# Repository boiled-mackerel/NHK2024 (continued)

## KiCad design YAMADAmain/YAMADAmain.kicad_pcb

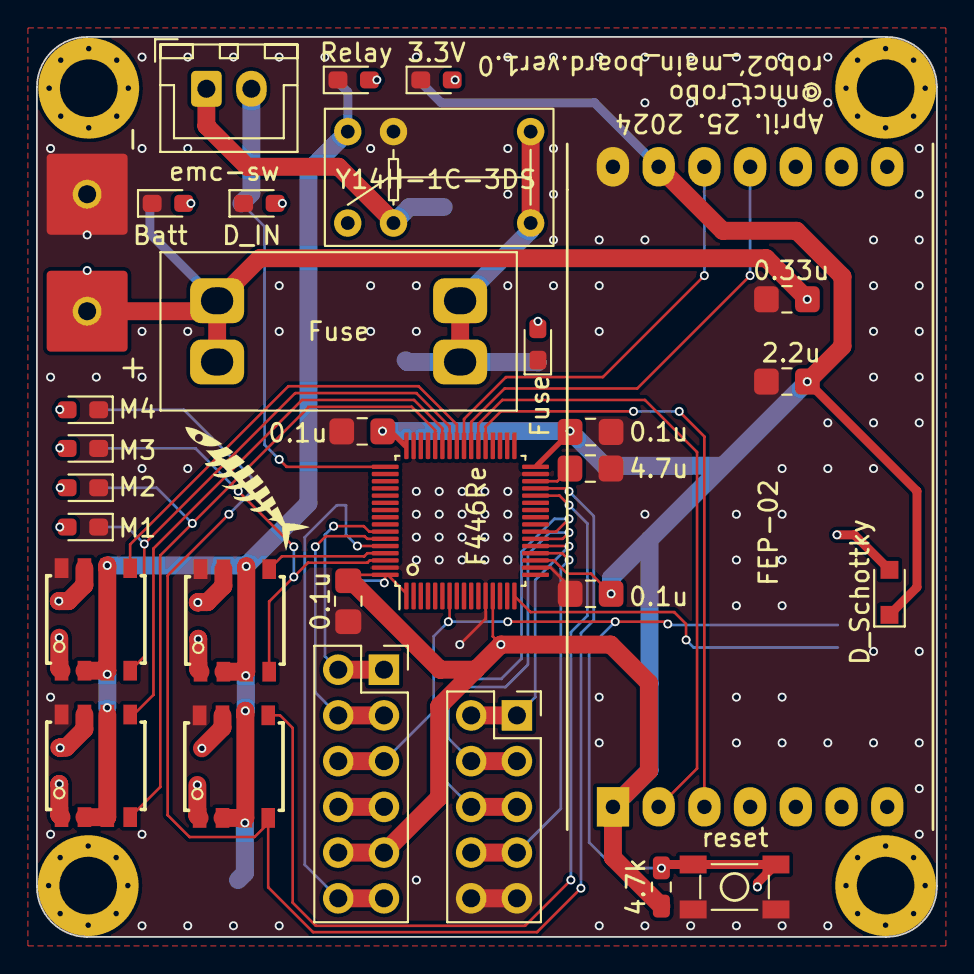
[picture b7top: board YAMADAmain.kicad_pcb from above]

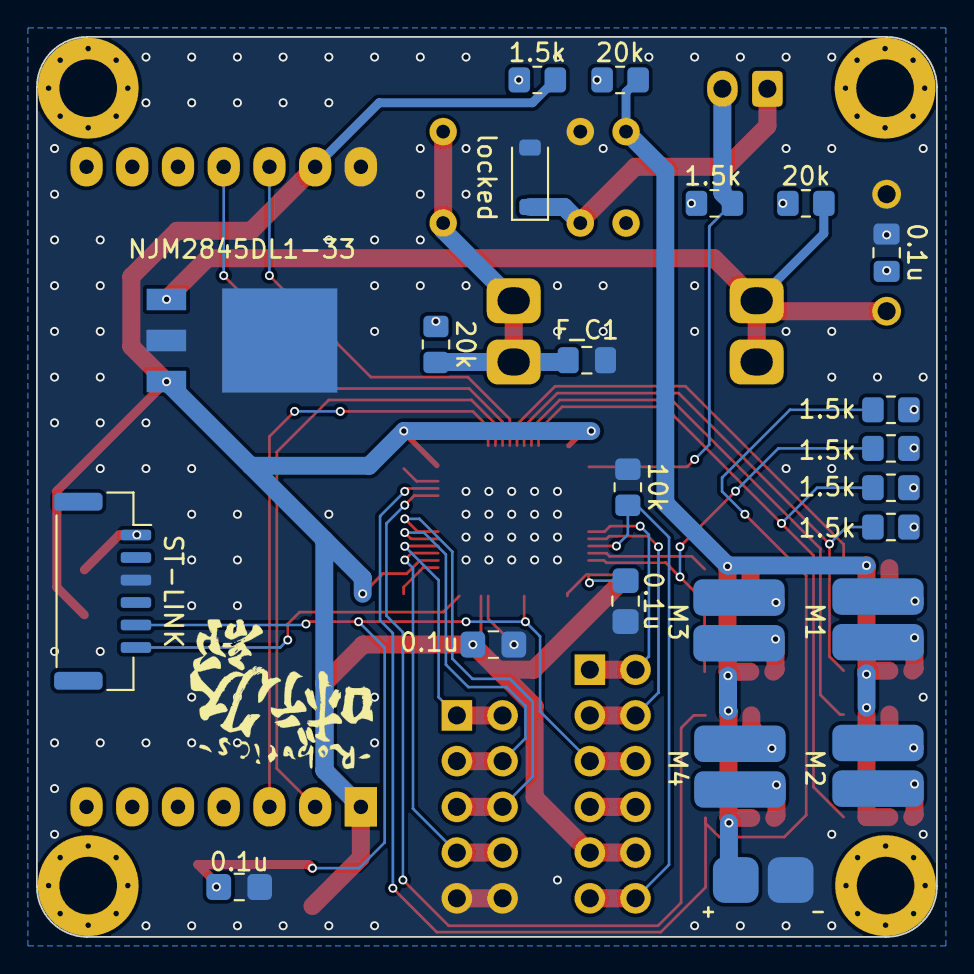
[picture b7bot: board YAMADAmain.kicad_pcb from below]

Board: 2 copper layers, 50.0 x 50.0 mm, 53 parts (22 on the bottom side), 48 nets.

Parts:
B_C1: 0.1u; C_0805_2012Metric_Pad1.18x1.45mm_HandSolder
C1: 0.33u; C_0805_2012
C2: 2.2u; C_0805_2012
D2: 3.3V; LED_0603_1608Metric_Pad1.05x0.95mm_HandSolder
D3: Batt; LED_0603_1608Metric_Pad1.05x0.95mm_HandSolder
D4: Fuse; LED_0603_1608Metric_Pad1.05x0.95mm_HandSolder
D5: D_IN; LED_0603_1608Metric_Pad1.05x0.95mm_HandSolder
D6: locked; D_SOD-123
D7: Relay; LED_0603_1608Metric_Pad1.05x0.95mm_HandSolder
D8: M4; LED_0603_1608Metric_Pad1.05x0.95mm_HandSolder
D9: M3; LED_0603_1608Metric_Pad1.05x0.95mm_HandSolder
D10: M2; LED_0603_1608Metric_Pad1.05x0.95mm_HandSolder
D11: M1; LED_0603_1608Metric_Pad1.05x0.95mm_HandSolder
F1: Fuse; FuseHolder_Carfuse
F_C1: 0.1u; C_0805_2012Metric_Pad1.18x1.45mm_HandSolder
J1: BATT; POWER_PAD
J2: Conn_02x06_Counter_Clockwise; PinSocket_2x06_P2.54mm_Vertical
J3: emc-sw; JST_XH_B2B-XH-A_1x02_P2.50mm_Vertical
J4: Conn_02x05_Counter_Clockwise; PinSocket_2x05_P2.54mm_Vertical
J5: motor1; min_motor
J6: motor2; min_motor
J7: motor3; min_motor
J8: motor4; min_motor
R1: 10k; R_0805_2012Metric_Pad1.20x1.40mm_HandSolder
R2, R5, R7, R8, R9, R10: 1.5k; R_0805_2012Metric_Pad1.20x1.40mm_HandSolder
R3, R4, R6: 20k; R_0805_2012Metric_Pad1.20x1.40mm_HandSolder
U1: NJM2845DL1-33
U2: FEP-02; FEP-02_PIN_SOCKET
U3: Y14H-1C-3DS
U4, U5, U6, U7: SOP8
U8: 4.7k; R_0603_1608
U9: D_Schottky; smd_diode_SOD-323_HandSoldering_cus10f30
U10: SW_DP3T; tact_sw_smd_skrpabe10
U11, U12, U17, U18, U19, U20, U21: 0.1u; C_0805_2012
U13: ST-LINK; JST_GH_SM06B-GHS-TB_1x06-1MP_P1.25mm_Horizontal
U15: 4.7u; C_0805_2012
U16: STM32F446RETx-stm32; LQFP-64_7x7mm_P0.4mm

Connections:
+3.3V: C2.1, J2.9, J2.10, R2.2, U1.3 (Vout), U2.1 (VCC(2.5v-5.5v)), U2.13 (PowerOn), U8.1, U9.1 (K), U12.1, U16.1 (VBAT), U16.13 (VDDA), U16.19 (VDD), U16.32 (VDD), U16.48 (VDD), U16.64 (VDD), U17.1, U18.1, U19.1, U20.1, U21.1
+5V: J2.7, J2.8
BAT: B_C1.1, C1.1, F1.1, J1.1, R3.2, U1.1 (Vin)
BOOT0: J2.11, J2.12, R1.1, U16.60 (BOOT0)
EMC_IN: J3.2, R5.2, U16.49 (SYS_JTCK-SWCLK/PA14)
FEP_INI: U2.11 (/INI), U16.39 (PC8/DCMI_D2/SDIO_D0/SYS_TRACED0/TIM3_CH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)
FEP_RST: U2.12 (/RST), U16.40 (PC9/DAC_EXTI9/DCMI_D3/I2C3_SDA/I2S_CKIN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)
Fuse_out: F1.2, F_C1.1, R4.1, U3.3, U3.6
GND: B_C1.2, C1.2, C2.2, D2.1 (K), D3.1 (K), D4.1 (K), D5.1 (K), D6.2 (A), D7.1 (K), D8.1 (K), D9.1 (K), D10.1 (K), D11.1 (K), F_C1.2, J1.2, J4.9, J4.10, R1.2, U1.2 (GND), U2.14 (GND), U3.5, U4.8 (GND), U5.8 (GND), U6.8 (GND), U7.8 (GND), U10.2, U10.4, U11.1, U12.2, U13.3, U15.2, U16.12 (VSSA), U16.18 (VSS), U16.31 (VSS), U16.47 (VSS), U16.63 (VSS), U17.2, U18.2, U19.2, U20.2, U21.2
M1FIN: R10.2, U4.4 (FIN), U16.42 (DAC_EXTI9/DCMI_D0/I2C3_SMBA/I2S2_CK/SAI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)
M1RIN: U4.5 (RIN), U16.41 (I2C3_SCL/RCC_MCO_1/TIM1_CH1/USART1_CK/U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)
M2FIN: R9.2, U5.4 (FIN), U16.44 (ADC1_EXTI11/ADC2_EXTI11/ADC3_EXTI11/CAN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)
M2RIN: U5.5 (RIN), U16.43 (DCMI_D1/TIM1_CH3/USART1_RX/USB_OTG_FS_I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)
M3FIN: R8.2, U6.4 (FIN), U16.62 (CAN1_TX/DAC_EXTI9/DCMI_D7/I2C1_SDA/I2S2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)
M3RIN: U6.5 (RIN), U16.61 (CAN1_RX/DCMI_D6/I2C1_SCL/SDIO_D4/TIM10_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)
M4FIN: R7.2, U7.4 (FIN), U16.29 (I2C2_SCL/I2S2_CK/SAI1_SCK_A/SPI2_SCK/TI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)
M4RIN: U7.5 (RIN), U16.28 (BOOT1/I2S3_SD/QUADSPI_CLK/SAI1_SD_A/SDI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)
MISO: J4.3, J4.4, U16.22 (ADC1_IN6/ADC2_IN6/DCMI_PIXCLK/I2S2_MCK/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)
MOSI: J4.5, J4.6, U16.23 (ADC1_IN7/ADC2_IN7/I2S1_SD/SPI1_MOSI/TIM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)
NSS: J4.7, J4.8, U16.20 (ADC1_IN4/ADC2_IN4/DAC_OUT1/DCMI_HSYNC/I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)
unnamed: D2.2 (A), R2.1
unnamed: D3.2 (A), R3.1
unnamed: D4.2 (A), R4.2
unnamed: D5.2 (A), R5.1
unnamed: D6.1 (K), J3.1, U3.2
unnamed: D7.2 (A), R6.1
unnamed: D8.2 (A), R7.1
unnamed: D9.2 (A), R8.1
unnamed: D10.2 (A), R9.1
unnamed: D11.2 (A), R10.1
unnamed: U9.2 (A), U13.1
unnamed: U15.1, U16.30 (VCAP_1)
PC_6_Serial6TX: U2.3 (TXD(DataIn)), U16.37 (PC6/DCMI_D0/FMPI2C1_SCL/I2S2_MCK/SDIO_D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)
PC_7_Serial6RX: U2.2 (RXD(DateOut)), U16.38 (PC7/DCMI_D1/FMPI2C1_SDA/I2S2_CK/I2S3_MC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)
RESET: J2.5, J2.6, U8.2, U10.1, U10.3, U11.2, U13.5, U16.7 (NRST)
Relay_out: R6.2, U3.4, U4.2 (VCC), U4.3 (VCC), U4.6 (VREF), U5.2 (VCC), U5.3 (VCC), U5.6 (VREF), U6.2 (VCC), U6.3 (VCC), U6.6 (VREF), U7.2 (VCC), U7.3 (VCC), U7.6 (VREF)
SCK: J4.1, J4.2, U16.21 (ADC1_IN5/ADC2_IN5/DAC_OUT2/I2S1_CK/SPI1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)
ST-LINK(TX): U13.6, U16.16 (ADC1_IN2/ADC2_IN2/ADC3_IN2/TIM2_CH3/TIM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)
U0RXD: J2.1, J2.2, U16.58 (CAN2_TX/CEC/DCMI_D5/I2C1_SCL/QUADSPI_BK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)
U0TXD: J2.3, J2.4, U16.59 (DCMI_VSYNC/I2C1_SDA/SPDIFRX_IN0/TIM4_CH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)
motor1_A: J5.1, U4.1 (OUT1)
motor1_B: J5.2, U4.7 (OUT2)
motor2_A: J6.1, U5.1 (OUT1)
motor2_B: J6.2, U5.7 (OUT2)
motor3_A: J7.1, U6.1 (OUT1)
motor3_B: J7.2, U6.7 (OUT2)
motor4_A: J8.1, U7.1 (OUT1)
motor4_B: J8.2, U7.7 (OUT2)
